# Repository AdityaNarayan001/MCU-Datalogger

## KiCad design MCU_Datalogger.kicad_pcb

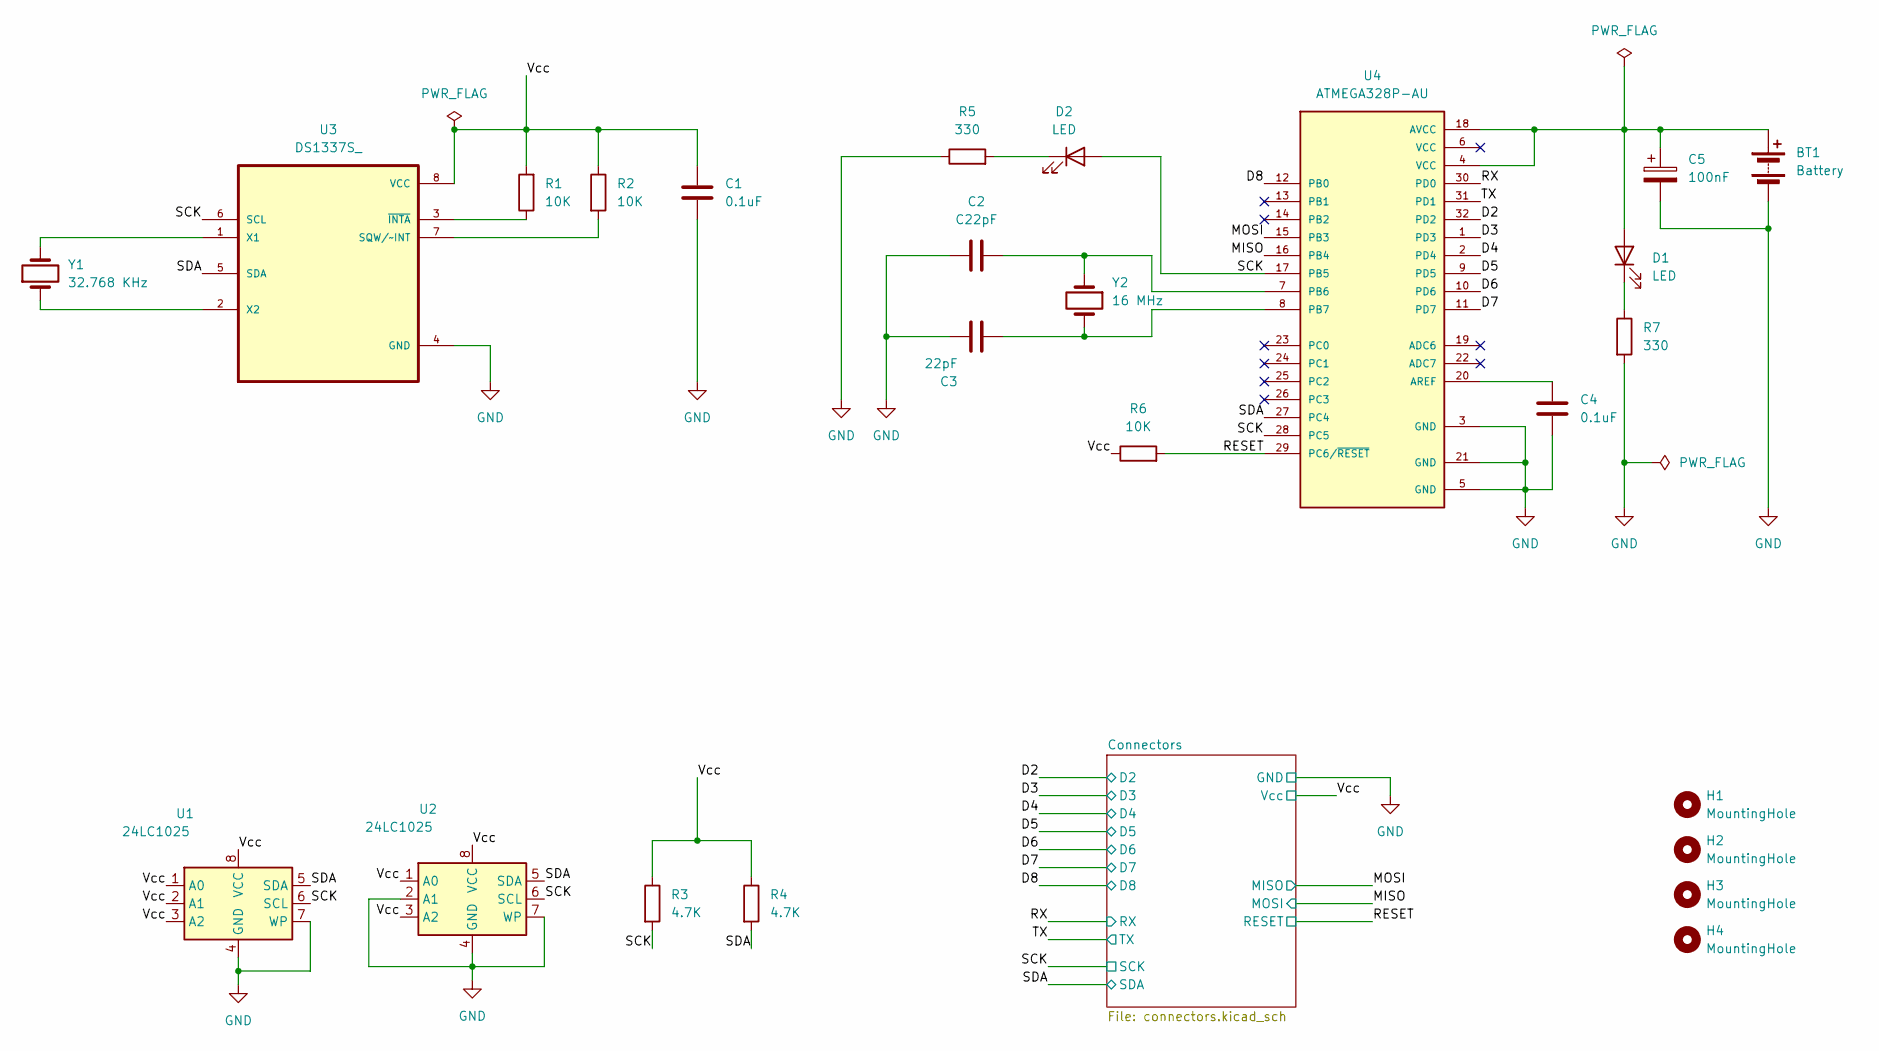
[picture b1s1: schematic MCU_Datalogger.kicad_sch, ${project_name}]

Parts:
BT1: Battery; PinHeader_1x02_P2.54mm_Vertical
C1, C4: 0.1uF; C_0805_2012Metric
C2: C22pF; C_0805_2012Metric
C3: 22pF; C_0805_2012Metric
C5: 100nF; C_0805_2012Metric
D1, D2: LED; LED_0805_2012Metric
H1, H2, H3, H4: MountingHole; MountingHole_2.1mm
R1, R2, R6: 10K; R_0805_2012Metric
R3, R4: 4.7K; R_0805_2012Metric
R5, R7: 330; R_0805_2012Metric
U1, U2: 24LC1025; SOIC-8_5.3x5.3mm_P1.27mm
U3: DS1337S_; SOIC127P600X175-8N
U4: ATMEGA328P-AU; QFP80P900X900X120-32N; PARTREV 8271A
Y1: 32.768 KHz; Crystal_SMD_5032-2Pin_5.0x3.2mm_HandSoldering
Y2: 16 MHz; Crystal_SMD_5032-2Pin_5.0x3.2mm_HandSoldering

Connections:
/D2: U4.32 (PD2); also elsewhere on the board
/D3: U4.1 (PD3); also elsewhere on the board
/D4: U4.2 (PD4); also elsewhere on the board
/D5: U4.9 (PD5); also elsewhere on the board
/D6: U4.10 (PD6); also elsewhere on the board
/D7: U4.11 (PD7); also elsewhere on the board
/D8: U4.12 (PB0); also elsewhere on the board
/MISO: U4.16 (PB4); also elsewhere on the board
/MOSI: U4.15 (PB3); also elsewhere on the board
/RESET: R6.2, U4.29 (PC6/~RESET); also elsewhere on the board
/RX: U4.30 (PD0); also elsewhere on the board
/SCK: D2.2 (A), R3.2, U1.6 (SCL), U2.6 (SCL), U3.6 (SCL), U4.17 (PB5), U4.28 (PC5); also elsewhere on the board
/SDA: R4.2, U1.5 (SDA), U2.5 (SDA), U3.5 (SDA), U4.27 (PC4); also elsewhere on the board
/TX: U4.31 (PD1); also elsewhere on the board
GND: BT1.2 (-), C1.2, C2.1, C3.1, C4.1, C5.2, R5.1, R7.2, U1.4 (GND), U1.7 (WP), U2.2 (A1), U2.4 (GND), U2.7 (WP), U3.4 (GND), U4.3 (GND), U4.5 (GND), U4.21 (GND); also elsewhere on the board
unnamed: D1.1 (K), R7.1
unnamed: D2.1 (K), R5.2
unnamed: R2.2, U3.7 (SQW/~INT)
unnamed: U3.1 (X1), Y1.2
unnamed: U3.2 (X2), Y1.1
unnamed: R1.1, U3.3 (~INTA)
unnamed: C4.2, U4.20 (AREF)
unnamed: C2.2, U4.7 (PB6), Y2.1
unnamed: C3.2, U4.8 (PB7), Y2.2

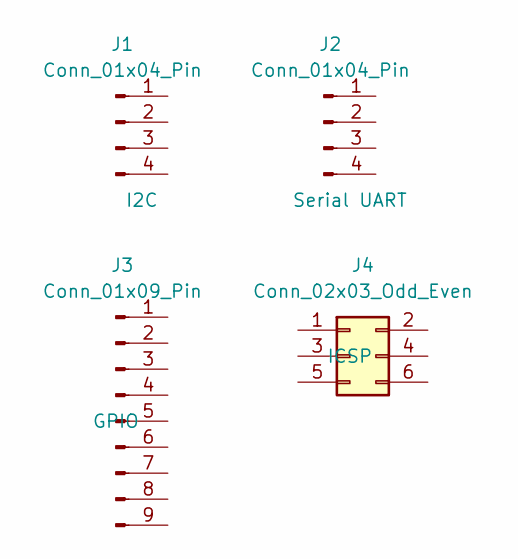
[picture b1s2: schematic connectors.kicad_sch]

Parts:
J1, J2: Conn_01x04_Pin
J3: Conn_01x09_Pin
J4: Conn_02x03_Odd_Even

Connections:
/D2: J3.1; also elsewhere on the board
/D3: J3.2; also elsewhere on the board
/D4: J3.3; also elsewhere on the board
/D5: J3.4; also elsewhere on the board
/D6: J3.5; also elsewhere on the board
/D7: J3.6; also elsewhere on the board
/D8: J3.7; also elsewhere on the board
/MISO: J4.4; also elsewhere on the board
/MOSI: J4.1; also elsewhere on the board
/RESET: J4.5; also elsewhere on the board
/RX: J2.3; also elsewhere on the board
/SCK: J1.4, J4.3; also elsewhere on the board
/SDA: J1.3; also elsewhere on the board
/TX: J2.4; also elsewhere on the board
GND: J1.1, J2.1, J3.8, J4.6; also elsewhere on the board

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
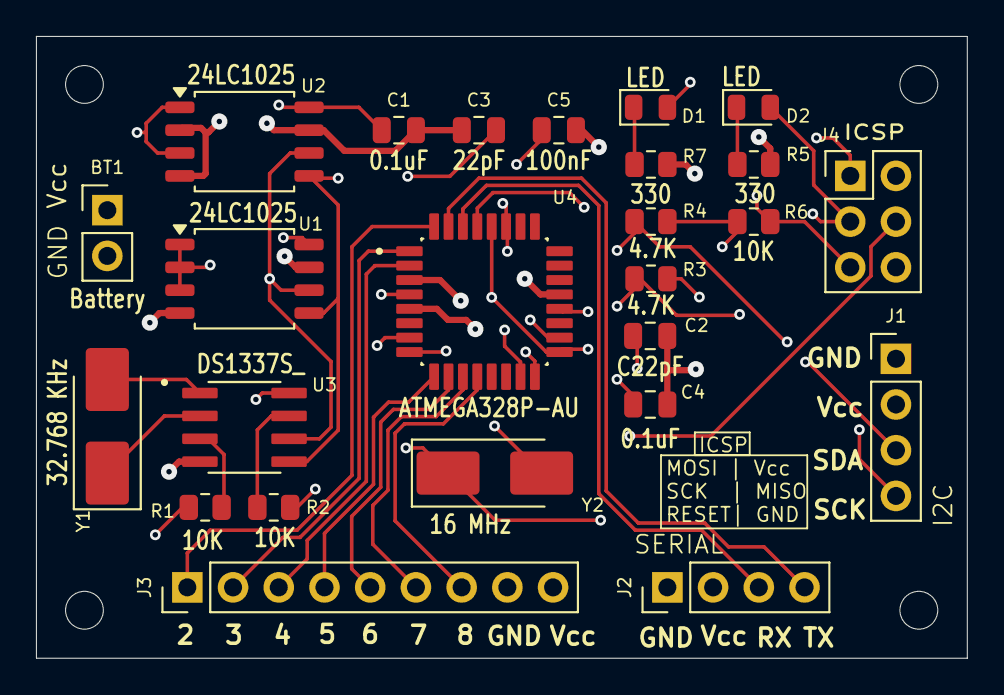
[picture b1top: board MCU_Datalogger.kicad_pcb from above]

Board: 4 copper layers, 51.7 x 34.5 mm, 29 parts (0 on the bottom side), 25 nets.
